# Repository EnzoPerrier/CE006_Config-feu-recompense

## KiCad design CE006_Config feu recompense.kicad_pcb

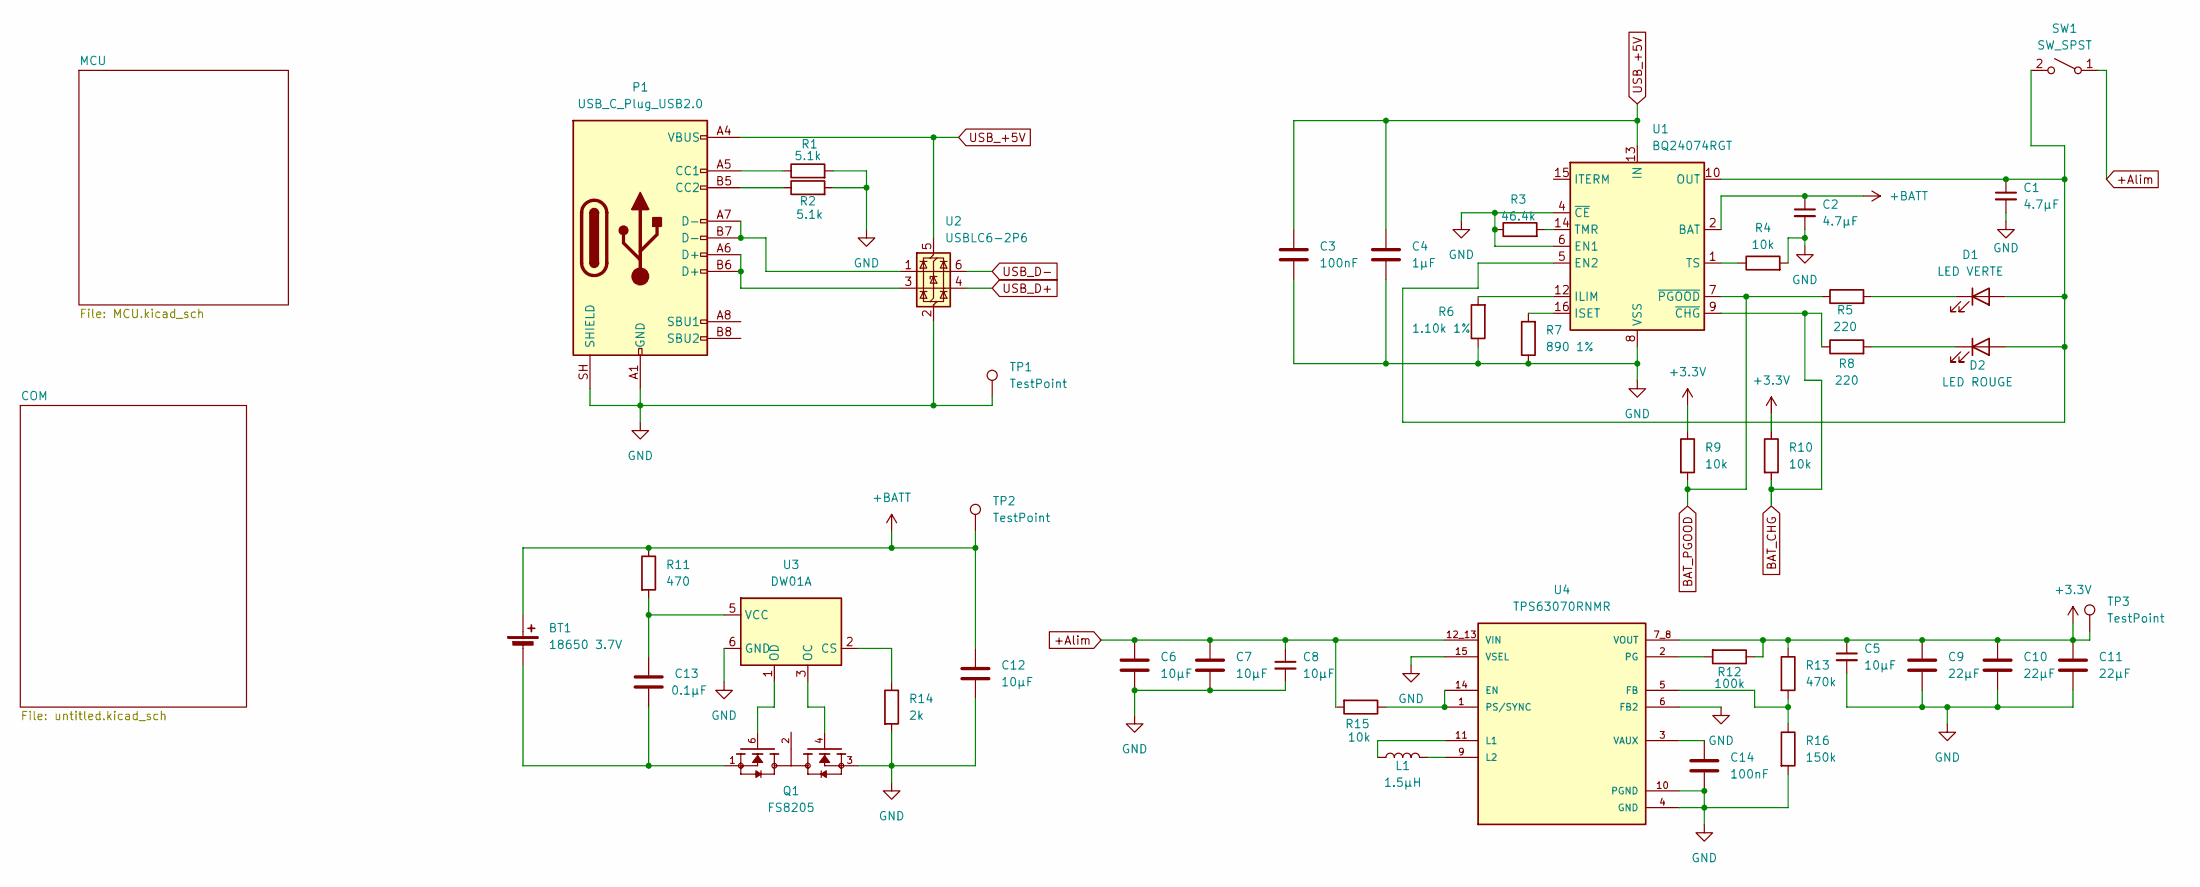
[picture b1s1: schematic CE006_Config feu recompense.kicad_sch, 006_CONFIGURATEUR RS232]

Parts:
BT1: 18650 3.7V; BatteryHolder_MPD_BK-18650-PC2
C1, C2: 4.7µF; C_0805_2012Metric
C3: 100nF; C_0805_2012Metric
C4: 1µF; C_1206_3216Metric
C5, C8: 10µF; C_0603_1608Metric
C6, C7: 10µF; C_0805_2012Metric
C9, C10, C11: 22µF; C_1210_3225Metric
C12: 10µF; C_1210_3225Metric
C13: 0.1µF; C_0805_2012Metric
C14: 100nF; C_0603_1608Metric
D1: LED VERTE; LED_1206_3216Metric
D2: LED ROUGE; LED_1206_3216Metric
L1: 1.5µH; IND_XFL4020-152MEC
P1: USB_C_Plug_USB2.0; USB_C_Receptacle_GCT_USB4105-xx-A_16P_TopMnt_Horizontal
Q1: FS8205; SOT95P280X145-6N; PARTREV 1.9
R1, R2: 5.1k; R_0805_2012Metric
R3: 46.4k; R_0805_2012Metric
R4, R9, R10, R15: 10k; R_0805_2012Metric
R5, R8: 220; R_0805_2012Metric
R6: 1.10k 1%; R_0805_2012Metric
R7: 890 1%; R_0805_2012Metric
R11: 470; R_0805_2012Metric
R12: 100k; R_0805_2012Metric
R13: 470k; R_0805_2012Metric
R14: 2k; R_0805_2012Metric
R16: 150k; R_0805_2012Metric
SW1: SW_SPST; JST_EH_B2B-EH-A_1x02_P2.50mm_Vertical
TP1: TestPoint; TestPoint_Pad_1.0x1.0mm
TP2, TP3: TestPoint; TestPoint_Pad_D1.0mm
U1: BQ24074RGT; VQFN-16-1EP_3x3mm_P0.5mm_EP1.6x1.6mm
U2: USBLC6-2P6; SOT-666
U3: DW01A; SOT-23-6
U4: TPS63070RNMR; VREG_TPS63070RNMR; PARTREV B

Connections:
+3.3V: C5.1, C9.1, C10.1, C11.1, R9.1, R10.1, R12.1, R13.1, TP3.1 (1_1), U4.7_8 (VOUT); also elsewhere on the board
+Alim: C6.1, C7.1, C8.1, R15.2, SW1.1 (A), U4.12_13 (VIN); also elsewhere on the board
+BATT: BT1.1 (+), C2.1, C12.1, R11.1, TP2.1 (1_1), U1.2 (BAT), U1.3 (BAT); also elsewhere on the board
BAT_CHG: R8.1, R10.2, U1.9 (~CHG); also elsewhere on the board
BAT_PGOOD: R5.1, R9.2, U1.7 (~PGOOD); also elsewhere on the board
GND: C1.2, C2.2, C3.2, C4.2, C5.2, C6.2, C7.2, C8.2, C9.2, C10.2, C11.2, C12.2, C14.2, P1.A1 (GND), P1.A12 (GND), P1.B1 (GND), P1.B12 (GND), P1.SH (SHIELD), Q1.3, R1.2, R2.2, R3.1, R4.2, R6.1, R7.1, R14.2, R16.2, TP1.1 (1_1), U1.4 (~CE), U1.6 (EN1), U1.8 (VSS), U1.17 (VSS), U2.2 (GND), U3.6 (GND), U4.4 (GND), U4.6 (FB2), U4.10 (PGND), U4.15 (VSEL); also elsewhere on the board
unnamed: BT1.2 (-), C13.2, Q1.1
unnamed: C1.1, D1.2 (A), D2.2 (A), SW1.2 (B), U1.5 (EN2), U1.10 (OUT), U1.11 (OUT)
unnamed: D1.1 (K), R5.2
unnamed: D2.1 (K), R8.2
unnamed: P1.A5 (CC1), R1.1
unnamed: P1.B5 (CC2), R2.1
unnamed: P1.A6 (D+), P1.B6 (D+), U2.3 (I/O2)
unnamed: P1.A7 (D-), P1.B7 (D-), U2.1 (I/O1)
unnamed: Q1.2, Q1.5
unnamed: R6.2, U1.12 (ILIM)
unnamed: R7.2, U1.16 (ISET)
unnamed: R3.2, U1.14 (TMR)
unnamed: R4.1, U1.1 (TS)
unnamed: R14.1, U3.2 (CS)
unnamed: Q1.4, U3.3 (OC)
unnamed: Q1.6, U3.1 (OD)
unnamed: C13.1, R11.2, U3.5 (VCC)
unnamed: R15.1, U4.1 (PS/SYNC), U4.14 (EN)
unnamed: R13.2, R16.1, U4.5 (FB)
unnamed: L1.1, U4.11 (L1)
unnamed: L1.2, U4.9 (L2)
unnamed: R12.2, U4.2 (PG)
unnamed: C14.1, U4.3 (VAUX)
USB_+5V: C3.1, C4.1, P1.A4 (VBUS), P1.A9 (VBUS), P1.B4 (VBUS), P1.B9 (VBUS), U1.13 (IN), U2.5 (VBUS)
USB_D+: U2.4 (I/O2); also elsewhere on the board
USB_D-: U2.6 (I/O1); also elsewhere on the board

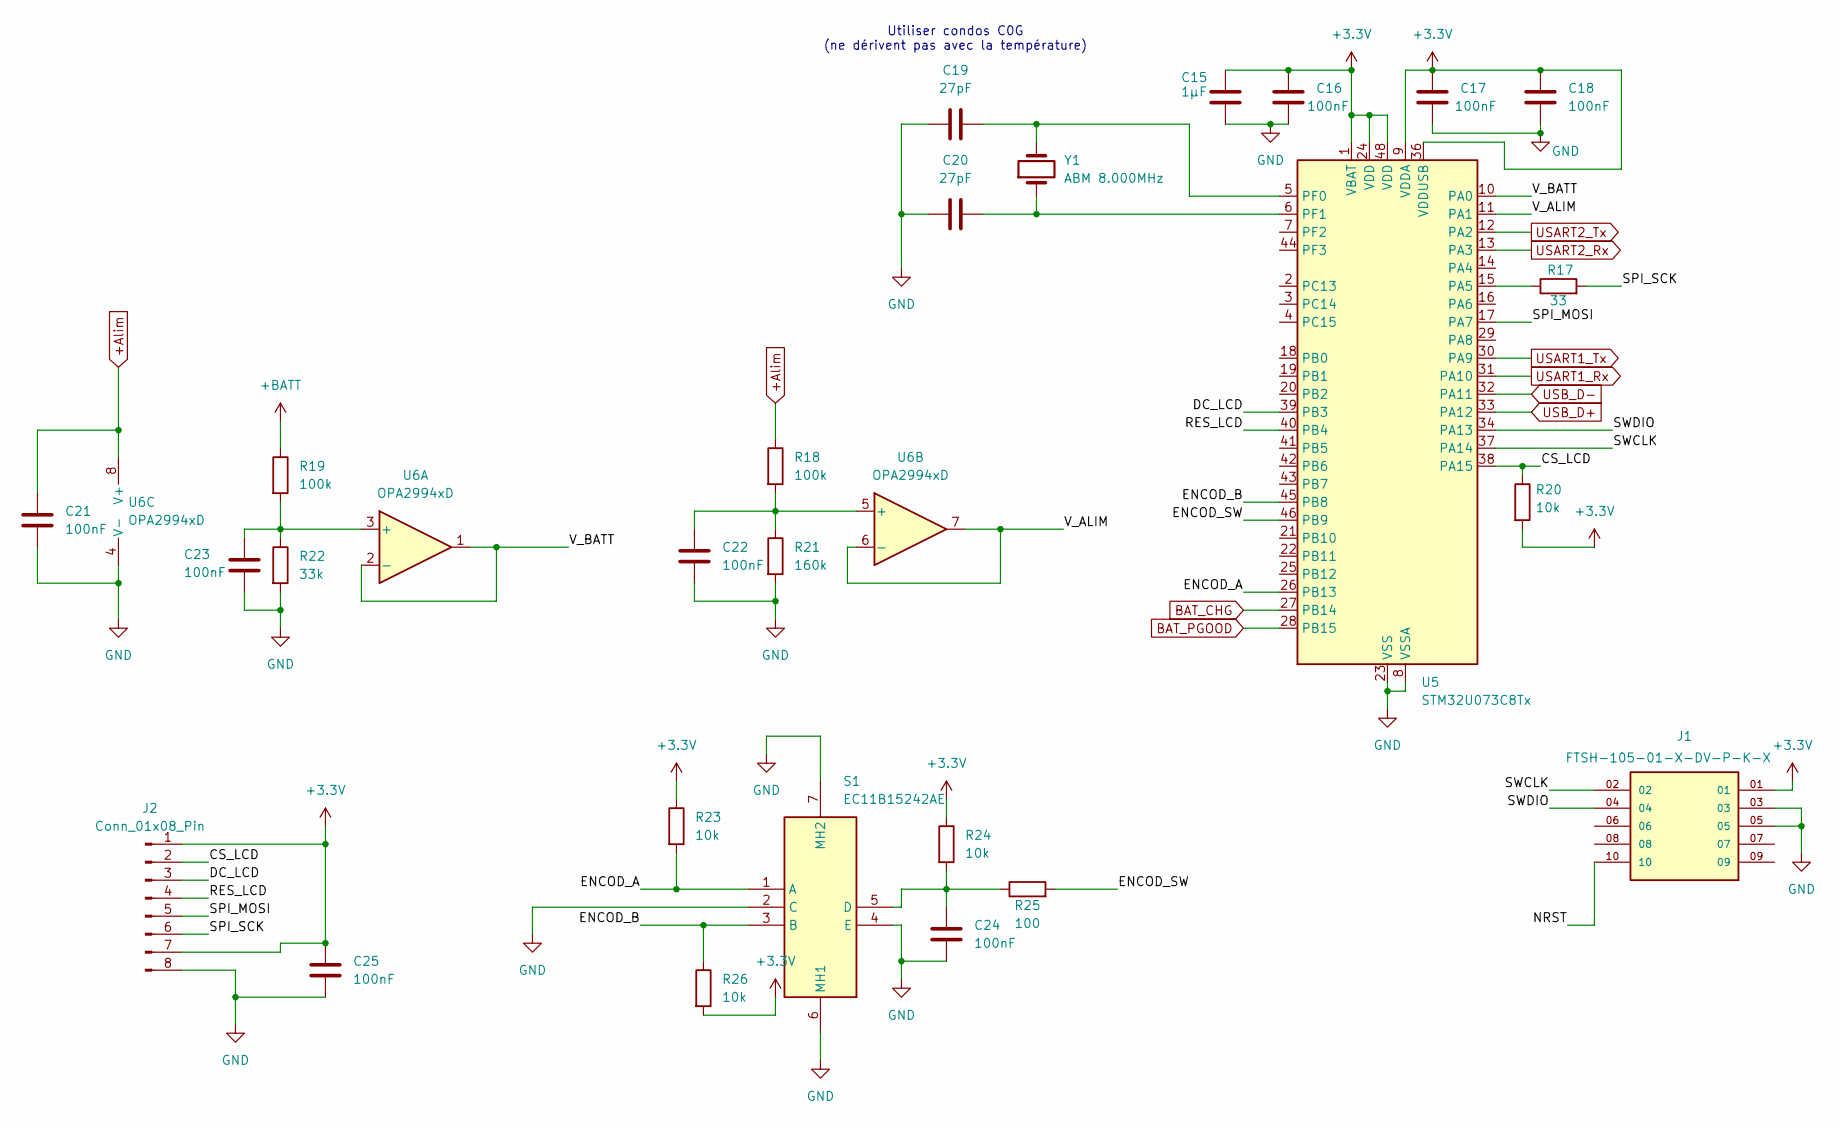
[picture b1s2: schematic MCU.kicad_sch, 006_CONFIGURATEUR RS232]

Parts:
C15: 1µF; C_1206_3216Metric
C16, C17, C18, C21, C22, C23, C24, C25: 100nF; C_0805_2012Metric
C19, C20: 27pF; C_0805_2012Metric
J1: FTSH-105-01-X-DV-P-K-X; SAMTEC_FTSH-105-01-X-DV-P-K-X; PARTREV H
J2: Conn_01x08_Pin; JST_EH_B8B-EH-A_1x08_P2.50mm_Vertical
R17: 33; R_0805_2012Metric
R18, R19: 100k; R_0805_2012Metric
R20, R23, R24, R26: 10k; R_0805_2012Metric
R21: 160k; R_0805_2012Metric
R22: 33k; R_0805_2012Metric
R25: 100; R_0805_2012Metric
S1: EC11B15242AE; Manufacturer_Part_Number EC11B15242AE; Mouser Part Number 688-EC11B15242AE
U5: STM32U073C8Tx; LQFP-48_7x7mm_P0.5mm
U6: OPA2994xD; SOIC-8_3.9x4.9mm_P1.27mm
Y1: ABM 8.000MHz; Crystal_SMD_Abracon_ABM3-2Pin_5.0x3.2mm_HandSoldering

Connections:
+3.3V: C15.1, C16.2, C17.2, C18.2, C25.1, J1.01, J2.1, J2.7, R20.2, R23.1, R24.1, R26.2, U5.1 (VBAT), U5.9 (VDDA), U5.24 (VDD), U5.36 (VDDUSB), U5.48 (VDD); also elsewhere on the board
+Alim: C21.1, R18.1, U6.8 (V+); also elsewhere on the board
+BATT: R19.1; also elsewhere on the board
/MCU/CS_LCD: J2.2, R20.1, U5.38 (PA15)
/MCU/DC_LCD: J2.3, U5.39 (PB3)
/MCU/ENCOD_A: R23.2, S1.1 (A), U5.26 (PB13)
/MCU/ENCOD_B: R26.1, S1.3 (B), U5.45 (PB8)
/MCU/ENCOD_SW: R25.2, U5.46 (PB9)
/MCU/RES_LCD: J2.4, U5.40 (PB4)
/MCU/SPI_MOSI: J2.5, U5.17 (PA7)
/MCU/SPI_SCK: J2.6, R17.2
/MCU/SWCLK: J1.02, U5.37 (PA14)
/MCU/SWDIO: J1.04, U5.34 (PA13)
/MCU/V_ALIM: U5.11 (PA1), U6.6 (-), U6.7
/MCU/V_BATT: U5.10 (PA0), U6.1, U6.2 (-)
BAT_CHG: U5.27 (PB14); also elsewhere on the board
BAT_PGOOD: U5.28 (PB15); also elsewhere on the board
GND: C15.2, C16.1, C17.1, C18.1, C19.1, C20.1, C21.2, C22.2, C23.2, C24.2, C25.2, J1.03, J1.05, J2.8, R21.2, R22.2, S1.2 (C), S1.4 (E), S1.6 (MH1), S1.7 (MH2), U5.8 (VSSA), U5.23 (VSS), U5.35 (VSS), U5.47 (VSS), U6.4 (V-); also elsewhere on the board
unnamed: C24.1, R24.2, R25.1, S1.5 (D)
unnamed: R17.1, U5.15 (PA5)
unnamed: C19.2, U5.5 (PF0), Y1.2
unnamed: C20.2, U5.6 (PF1), Y1.1
unnamed: C23.1, R19.2, R22.1, U6.3 (+)
unnamed: C22.1, R18.2, R21.1, U6.5 (+)
USART1_Rx: U5.31 (PA10); also elsewhere on the board
USART1_Tx: U5.30 (PA9); also elsewhere on the board
USART2_Rx: U5.13 (PA3); also elsewhere on the board
USART2_Tx: U5.12 (PA2); also elsewhere on the board
USB_D+: U5.33 (PA12); also elsewhere on the board
USB_D-: U5.32 (PA11); also elsewhere on the board

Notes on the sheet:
Utiliser condos C0G (ne dérivent pas avec la température)

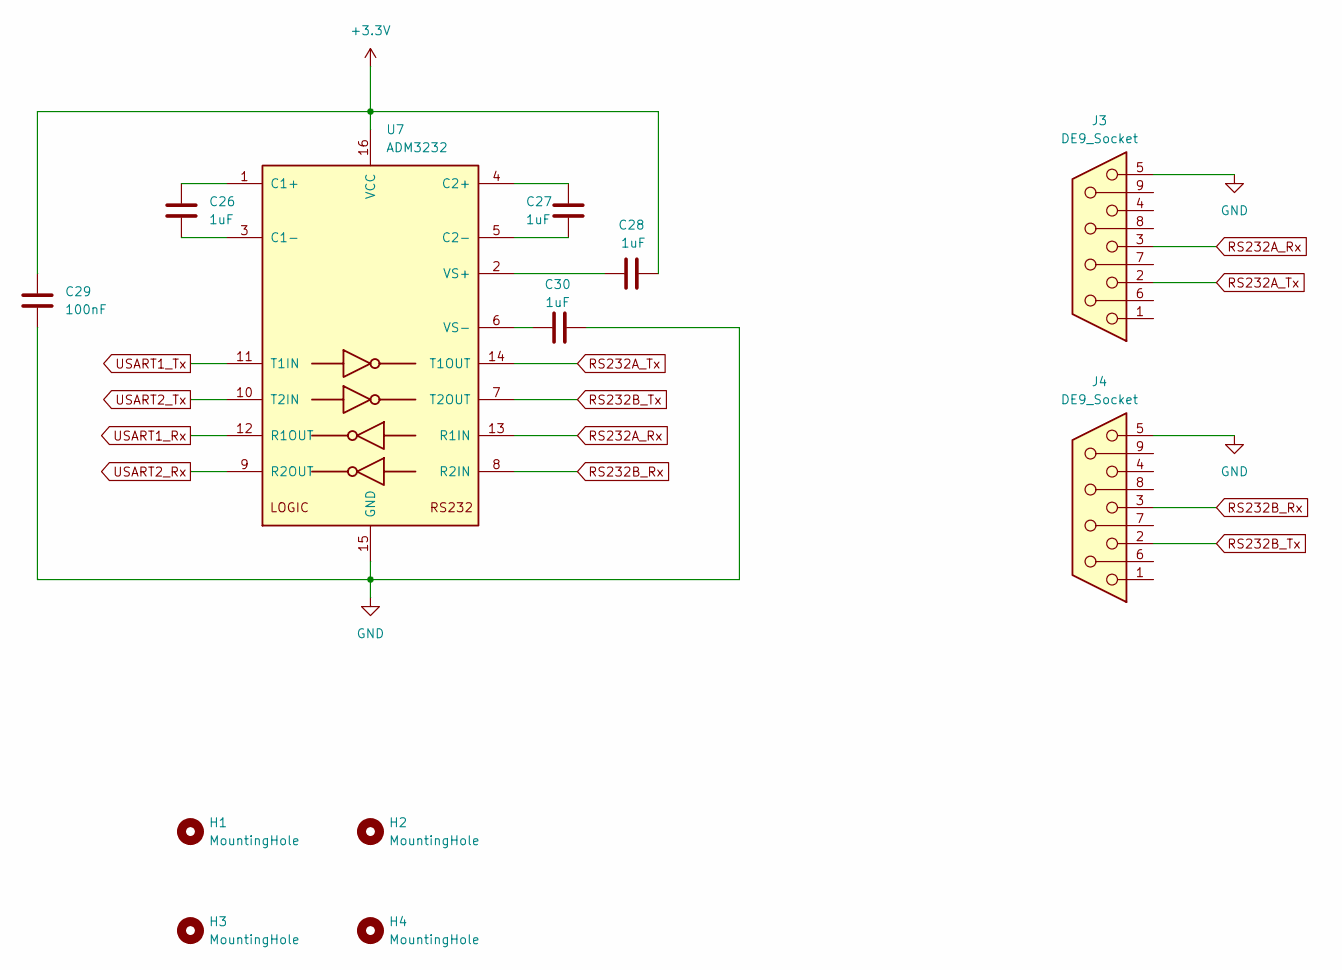
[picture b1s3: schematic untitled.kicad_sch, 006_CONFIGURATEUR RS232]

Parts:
C26, C27, C28, C30: 1uF; C_0805_2012Metric_Pad1.18x1.45mm_HandSolder
C29: 100nF; C_0805_2012Metric_Pad1.18x1.45mm_HandSolder
H1, H2, H3, H4: MountingHole; MountingHole_3.2mm_M3
J3, J4: DE9_Socket; DSUB-9_Socket_Horizontal_P2.77x2.84mm_EdgePinOffset7.70mm_H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
U7: ADM3232; SOP-16_4.4x10.4mm_P1.27mm

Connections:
+3.3V: C28.2, C29.1, U7.16 (VCC); also elsewhere on the board
GND: C29.2, C30.2, J3.5, J4.5, U7.15 (GND); also elsewhere on the board
unnamed: C26.1, U7.1 (C1+)
unnamed: C26.2, U7.3 (C1-)
unnamed: C27.1, U7.4 (C2+)
unnamed: C27.2, U7.5 (C2-)
unnamed: C28.1, U7.2 (VS+)
unnamed: C30.1, U7.6 (VS-)
RS232A_Rx: J3.3, U7.13 (R1IN)
RS232A_Tx: J3.2, U7.14 (T1OUT)
RS232B_Rx: J4.3, U7.8 (R2IN)
RS232B_Tx: J4.2, U7.7 (T2OUT)
USART1_Rx: U7.12 (R1OUT); also elsewhere on the board
USART1_Tx: U7.11 (T1IN); also elsewhere on the board
USART2_Rx: U7.9 (R2OUT); also elsewhere on the board
USART2_Tx: U7.10 (T2IN); also elsewhere on the board

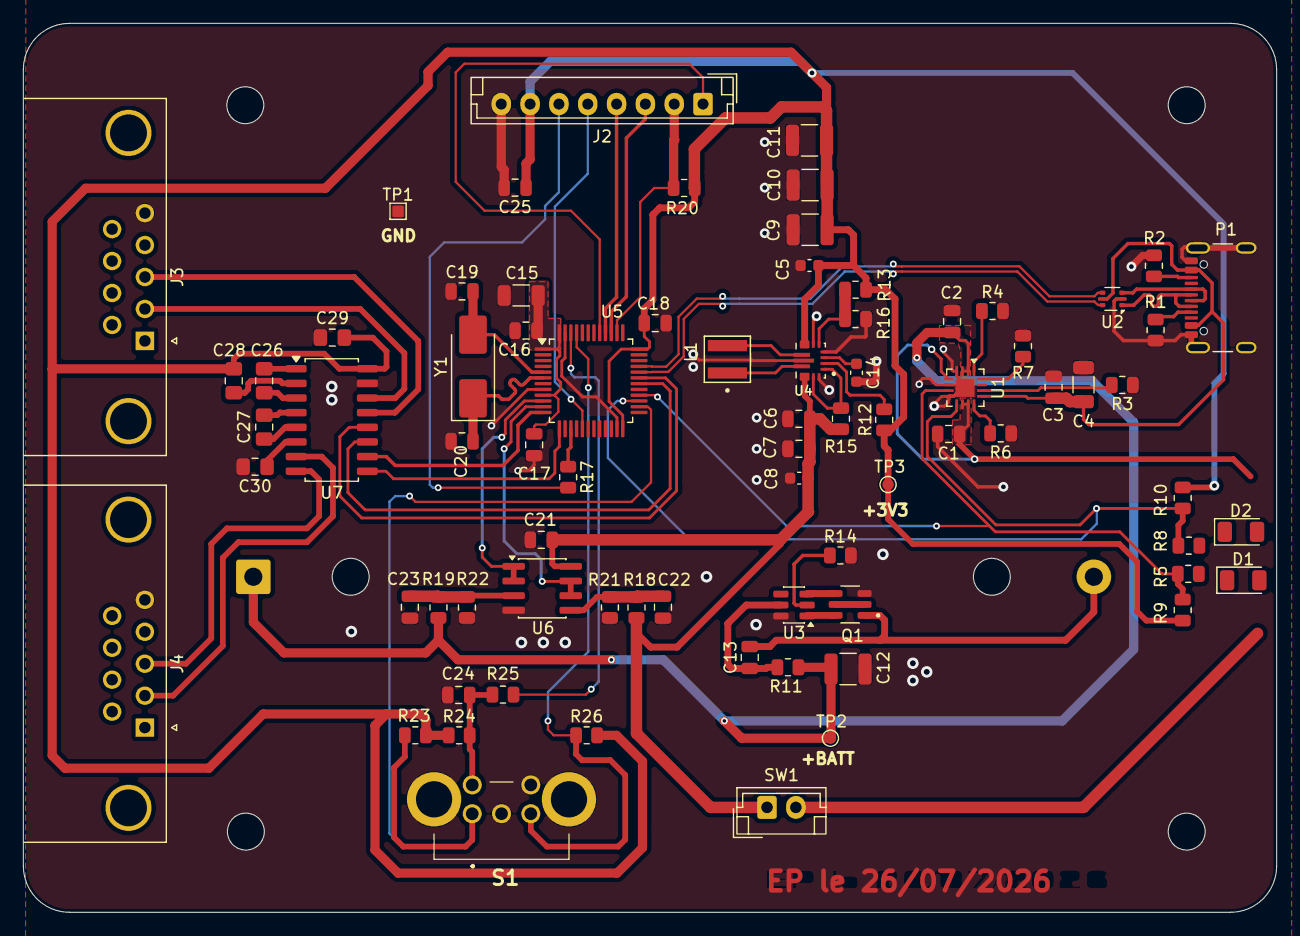
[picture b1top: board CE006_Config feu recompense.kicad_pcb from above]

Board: 2 copper layers, 108.7 x 77.1 mm, 82 parts (1 on the bottom side), 62 nets.

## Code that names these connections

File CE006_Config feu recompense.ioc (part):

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Mcu.Name=STM32U073C8Tx
Mcu.Package=LQFP48
Mcu.UserName=STM32U073C8Tx
PA0.GPIOParameters=GPIO_Label
PA0.GPIO_Label=V_BATT
PA0.Mode=IN4
PA0.Signal=ADC1_IN4
PA1.GPIOParameters=GPIO_Label
PA1.GPIO_Label=V_ALIM
PA1.Mode=IN5
PA1.Signal=ADC1_IN5
PA10.Mode=Asynchronous
PA10.Signal=USART1_RX
PA11\ [PA9].Mode=Device
PA11\ [PA9].Signal=USB_DM
PA12\ [PA10].Mode=Device
PA12\ [PA10].Signal=USB_DP
PA13\ (SWDIO).GPIOParameters=GPIO_Label
PA13\ (SWDIO).GPIO_Label=SWDIO
PA13\ (SWDIO).Signal=DEBUG_JTMS-SWDIO
PA14\ (SWCLK).GPIOParameters=GPIO_Label
PA14\ (SWCLK).GPIO_Label=SWCLK
PA14\ (SWCLK).Signal=DEBUG_JTCK-SWCLK
PA15.GPIOParameters=GPIO_Label
PA15.GPIO_Label=CS_LCD
PA15.Signal=GPIO_Output
PA2.Mode=Asynchronous
PA2.Signal=USART2_TX
PA3.Mode=Asynchronous
PA3.Signal=USART2_RX
PA5.GPIOParameters=GPIO_Label
PA5.GPIO_Label=SPI_SCK
PA5.Mode=TX_Only_Simplex_Unidirect_Master
PA5.Signal=SPI1_SCK
PA7.GPIOParameters=GPIO_Label
PA7.GPIO_Label=SPI_MOSI
PA7.Mode=TX_Only_Simplex_Unidirect_Master
PA7.Signal=SPI1_MOSI
PA9.Mode=Asynchronous
PA9.Signal=USART1_TX
PB13.GPIOParameters=GPIO_Label
PB13.GPIO_Label=ENCOD_A
PB13.Mode=Encoder_mode_occur1
PB13.Signal=LPTIM3_IN1
PB14.GPIOParameters=GPIO_Label
PB14.GPIO_Label=BAT_CHG
PB14.Signal=GPIO_Input
PB15.GPIOParameters=GPIO_Label
PB15.GPIO_Label=BAT_PGOOD
PB15.Signal=GPIO_Input
PB3.GPIOParameters=GPIO_Label
PB3.GPIO_Label=DC_LCD
PB3.Signal=GPIO_Output
PB4.GPIOParameters=GPIO_Label
PB4.GPIO_Label=RES_LCD
PB4.Signal=GPIO_Output
PB8.GPIOParameters=GPIO_Label
PB8.GPIO_Label=ENCOD_B
PB8.Mode=Encoder_mode_occur1
PB8.Signal=LPTIM3_IN2
PB9.GPIOParameters=GPIO_Label
PB9.GPIO_Label=ENCOD_SW
PB9.Signal=GPIO_Input
PF0-OSC_IN.Mode=HSE-External-Oscillator
PF0-OSC_IN.Signal=RCC_OSC_IN
PF1-OSC_OUT.Mode=HSE-External-Oscillator
PF1-OSC_OUT.Signal=RCC_OSC_OUT
RCC.HSE_VALUE=4000000
RCC.SYSCLKFreq_VALUE=16000000
board=custom
